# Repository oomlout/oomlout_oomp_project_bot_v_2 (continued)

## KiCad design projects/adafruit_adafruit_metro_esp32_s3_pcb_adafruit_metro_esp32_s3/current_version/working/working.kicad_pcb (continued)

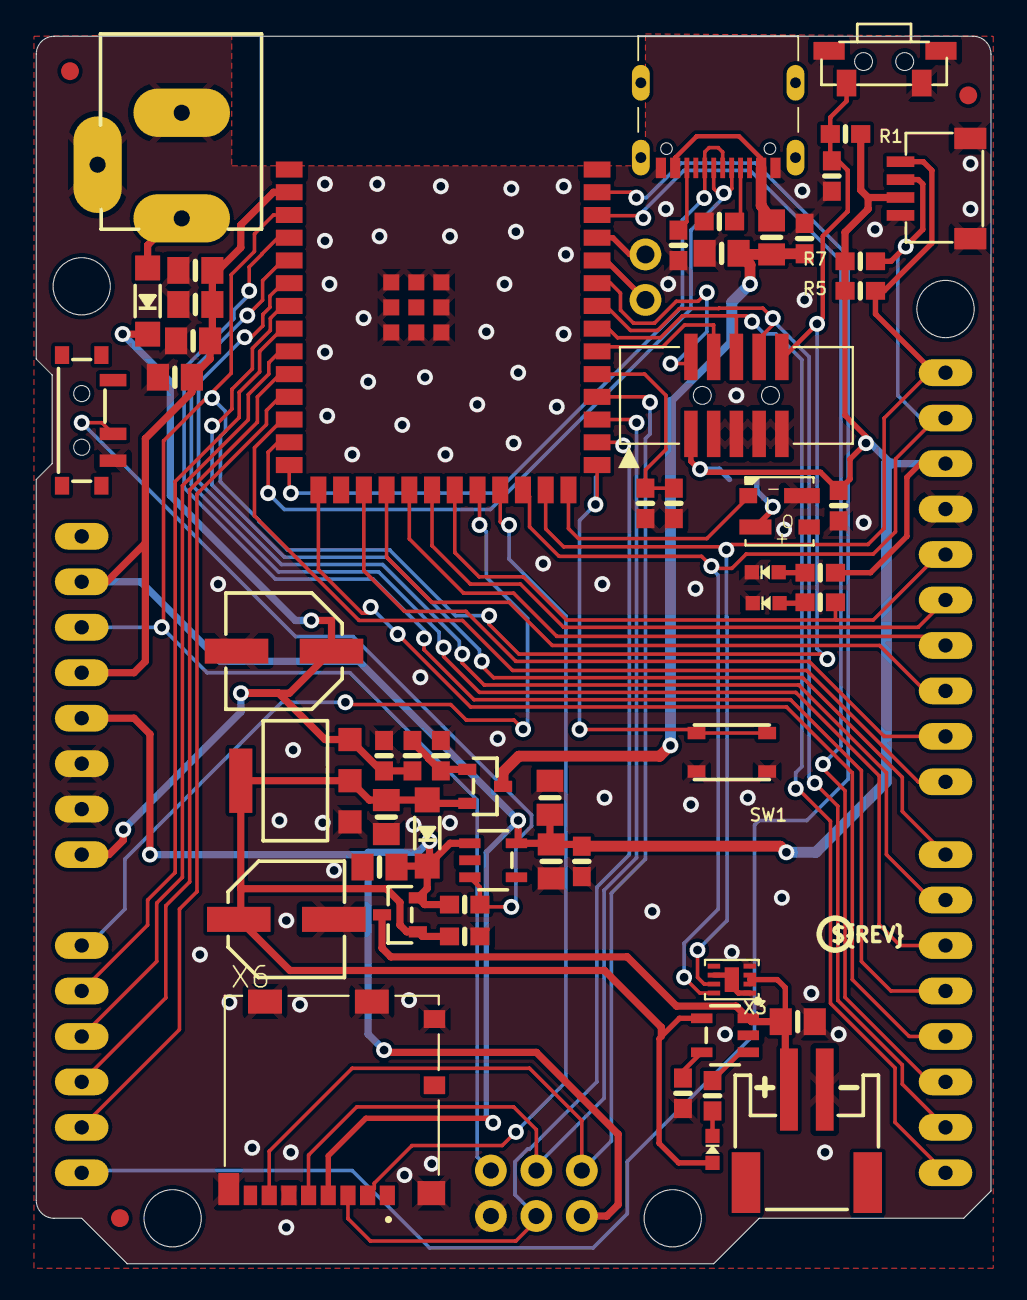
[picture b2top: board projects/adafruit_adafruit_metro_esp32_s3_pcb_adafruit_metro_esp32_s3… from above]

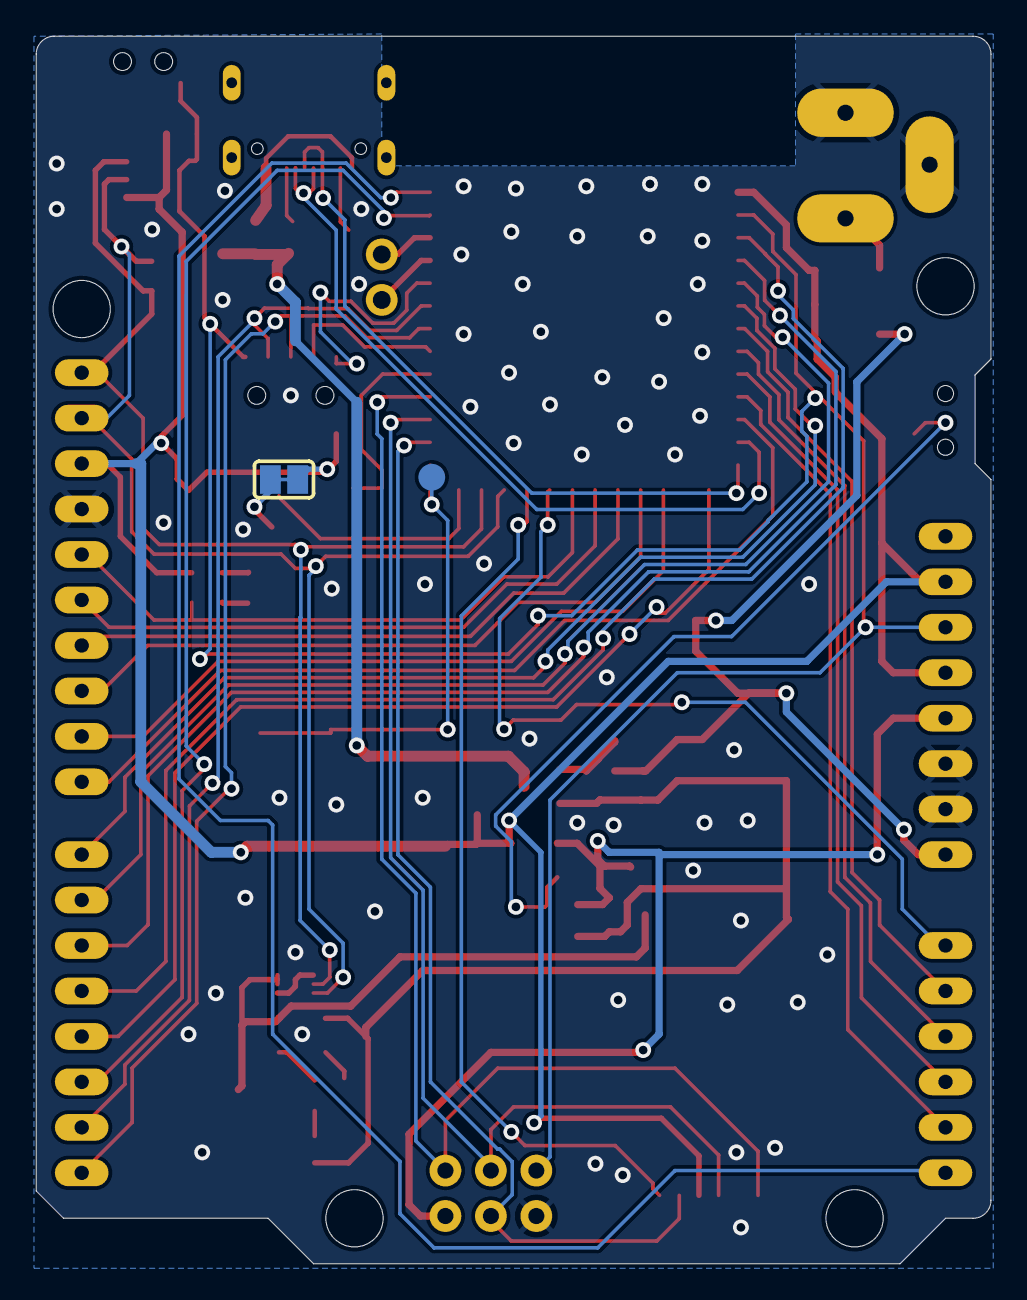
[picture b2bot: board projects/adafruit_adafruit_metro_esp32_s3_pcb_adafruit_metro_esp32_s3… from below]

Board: 2 copper layers, 53.3 x 68.6 mm, 73 parts (3 on the bottom side), 55 nets.

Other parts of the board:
@HOLE0, @HOLE1, @HOLE2, @HOLE3: (no value)
U$15: PCBFEAT-REV-040
U$52: METROS3_TOP
U$58: METROS3_BOT

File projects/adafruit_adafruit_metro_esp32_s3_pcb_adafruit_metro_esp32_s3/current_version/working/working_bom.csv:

"Id";"Designator";"Footprint";"Quantity";"Designation";"Supplier and ref";
1;"Q2,Q1";"SOT23-R";2;"DMG3415U-7";;;
2;"C15,C2,C12";"0603-NO";3;"0.1uF";;;
3;"R5,R6,R2,R7,R9,R1";"0603-NO";6;"10K";;;
4;"X3";"TDFN8_2X2MM";1;"MAX17048/T";;;
5;"C3,C17,C7,C13,C11,C4,C18,C10,C1,C8";"0805-NO";10;"10uF";;;
6;"X5";"DCJACK_2MM_PTH";1;"2.1mm";;;
7;"SW1";"BTN_RKB2_4.6X2.8";1;"RKB2";;;
8;"U4";"SOT23-5";1;"AP2112(3.3V)";;;
9;"@HOLE2,@HOLE0,@HOLE3,@HOLE1";"";4;"";;;
10;"JP2";"1X02_ROUND";1;"UART";;;
11;"L0";"CHIPLED_0603_NOOUTLINE";1;"RED";;;
12;"SW4";"SPDT_SMT_SSSS811101";1;"SPDT R/A";;;
13;"R17";"0603-NO";1;"1Meg";;;
14;"U2";"SOT23-5";1;"MCP73831T-2ACI/OT";;;
15;"U1";"SOT223-R";1;"NCP1117ST50T3G";;;
16;"R12,R15,R16,R14";"0603-NO";4;"100K";;;
17;"ON0";"CHIPLED_0603_NOOUTLINE";1;"GREEN";;;
18;"U5";"S3-WROOM32";1;"ESP32-S3-WROOM";;;
19;"R8,R3";"0603-NO";2;"5.1K";;;
20;"IOH0";"1X10_OVALWAVE";1;"1x10 F";;;
21;"R4";"0603-NO";1;"2.2K";;;
22;"FD1,FD2,FD3";"FIDUCIAL_1MM";3;"FIDUCIAL_1MM";;;
23;"X1";"JSTPH2_BATT";1;"JSTPH";;;
24;"CHG1";"CHIPLED_0603_NOOUTLINE";1;"ORANGE";;;
25;"PC2,PC1";"PANASONIC_D";2;"47uF/25V";;;
26;"X6";"MOLEX_104031-0811";1;"MicroSD";;;
27;"POWER0,IOL0";"1X08_OVALWAVE";2;"1x8 F";;;
28;"AD0";"1X06_OVALWAVE";1;"1x6 F";;;
29;"C14,C5,C6";"0603-NO";3;"1uF";;;
30;"SW3";"SPST_TACTILE_RA";1;"RA_TACT";;;
31;"CONN1";"JST_SH4";1;"STEMMA_I2C_QT";;;
32;"F2";"0805-NO";1;"500mA";;;
33;"X2";"2X05_1.27MM_BOX_POSTS";1;"2x5 0.05in";;;
34;"D1,D4";"SOD-123";2;"MBR540";;;
35;"U$15";"PCBFEAT-REV-040";1;"";;;
36;"ICSP0";"2X03_ROUND_70MIL";1;"3x2 M";;;
37;"U$52";"METROS3_TOP";1;"";;;
38;"X4";"USB_C_CUSB31-CFM2AX-01-X";1;"USB C";;;
39;"LED1";"LED3535_FULLPADS";1;"WS2812B_3535FULL";;;
40;"TP1";"TESTPOINT_ROUND_1.5MM_NO";1;"";;;
41;"U$58";"METROS3_BOT";1;"";;;
42;"SJ1";"SOLDERJUMPER_CLOSEDWIRE";1;"";;;

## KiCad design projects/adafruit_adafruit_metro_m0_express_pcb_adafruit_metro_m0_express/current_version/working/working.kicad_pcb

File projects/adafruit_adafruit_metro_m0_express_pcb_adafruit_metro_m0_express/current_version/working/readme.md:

# adafruit_metro_m0_express_pcb
 
## summary 
* id: adafruit_adafruit_metro_m0_express_pcb_adafruit_metro_m0_express
* user: adafruit
* name: adafruit_metro_m0_express_pcb
* board: adafruit_metro_m0_express
* repo: https://github.com/adafruit/Adafruit-Metro-M0-Express-PCB

* src_file_repo_sch: 
* src_file_repo_sch_link: https://github.com/adafruit/Adafruit-Metro-M0-Express-PCB/tree/master/
* full details link: https://github.com/oomlout/oomlout_oomp_project_bot_v_2/tree/main/projects/adafruit_adafruit_metro_m0_express_pcb_adafruit_metro_m0_express/current_version/working  

## schematic  
  
[schematic (pdf)](working_schematic.pdf) 

## pcb  

[board (pdf)](working.pdf)  

## working_bom
| Id | Designator | Footprint | Quantity | Designation | Supplier and ref |  | None | 
| --- | --- | --- | --- | --- | --- | --- | --- | 
| 1 | FB2,FB1 | 0805-NO | 2 | FERRITE |  |  | [''] | 
| 2 | R1 | RESPACK_4X0603 | 1 | 100K |  |  | [''] | 
| 3 | @HOLE0,@HOLE1,@HOLE3,@HOLE2 |  | 4 |  |  |  | [''] | 
| 4 | FD1,FD2,FD3 | FIDUCIAL_1MM | 3 | FIDUCIAL_1MM |  |  | [''] | 
| 5 | X3 | 4UCONN_20329_V2 | 1 | 20329 |  |  | [''] | 
| 6 | U$14 | PCBFEAT-REV-040 | 1 |  |  |  | [''] | 
| 7 | C11,C14,C6,C10,C4,C13,C12,C2,C9 | 0805-NO | 9 | 0.1uF |  |  | [''] | 
| 8 | R11,R3 | 0805-NO | 2 | 330R |  |  | [''] | 
| 9 | X5 | DCJACK_2MM_PTH | 1 | 2.1mm |  |  | [''] | 
| 10 | PC2 | PANASONIC_D | 1 | 47uF+/6.3V+ |  |  | [''] | 
| 11 | R4 | 0805-NO | 1 | 1K |  |  | [''] | 
| 12 | SW1 | SPDT_SMT_SSSS811101 | 1 |  |  |  | [''] | 
| 13 | TXLED0,RXLED0 | CHIPLED_0805_NOOUTLINE | 2 | YELLOW |  |  | [''] | 
| 14 | IOL0,POWER0 | 1X08_OVALWAVE | 2 | 20610 |  |  | [''] | 
| 15 | R7,R5 | 0805-NO | 2 | 10K |  |  | [''] | 
| 16 | L0 | CHIPLED_0805_NOOUTLINE | 1 | RED |  |  | [''] | 
| 17 | U1 | SOT223-R | 1 | NCP1117ST50T3G |  |  | [''] | 
| 18 | F2 | R1206 | 1 | 500mA |  |  | [''] | 
| 19 | IOH0 | 1X10_OVALWAVE | 1 | 20611 |  |  | [''] | 
| 20 | X2 | 2X05_1.27MM_BOX_POSTS | 1 | 2x5 0.05 SWD" |  |  | [''] | 
| 21 | T2,TR1 | SOT-23 | 2 | DMP3098L-7 |  |  | [''] | 
| 22 | C1 | 0805-NO | 1 | 1uF |  |  | [''] | 
| 23 | C7,C5 | 0805-NO | 2 | 22pF |  |  | [''] | 
| 24 | U$30 | METRO_M0_FRONT | 1 |  |  |  | [''] | 
| 25 | JP1 | 1X01_ROUND | 1 |  |  |  | [''] | 
| 26 | C8,C3 | 0805-NO | 2 | 10uF |  |  | [''] | 
| 27 | ICSP0 | 2X03_ROUND_70MIL | 1 | 3x2 M |  |  | [''] | 
| 28 | R2 | RESPACK_4X0603 | 1 | 1K |  |  | [''] | 
| 29 | PC1 | PANASONIC_D | 1 | 47uF/25V |  |  | [''] | 
| 30 | Y1 | CRYSTAL_8X3.8 | 1 | 32.768KHz |  |  | [''] | 
| 31 | U$1 | TQFN48_7MM | 1 | ATSAMD21G18_QFN |  |  | [''] | 
| 32 | AD0 | 1X06_OVALWAVE | 1 | 20609 |  |  | [''] | 
| 33 | LED1 | LED3535 | 1 | WS2812B3535 |  |  | [''] | 
| 34 | ON0 | CHIPLED_0805_NOOUTLINE | 1 | GREEN |  |  | [''] | 
| 35 | RESET0 | EVQ-Q2 | 1 | EVQQ 6mm |  |  | [''] | 
| 36 | D1 | SOD-123 | 1 | MBR120 |  |  | [''] | 
| 37 | IC3 | SOT23-5 | 1 | 74LVC1G125D |  |  | [''] | 
| 38 | U3 | SOIC8_208MIL | 1 | SPI Flash |  |  | [''] | 
| 39 | U2 | SOT23-DBV | 1 | AP2112K-3.3 |  |  | [''] | 
| 40 | U$11 | METRO_M0_BACK | 1 |  |  |  | [''] | 
| 41 | TP1,TP2 | TESTPOINT_ROUND_1.5MM | 2 |  |  |  | [''] | 
| 42 | GROUND1 | SJ | 1 |  |  |  | [''] | 

## bom_schematic
| Ref | Qnty | Value | Cmp name | Footprint | Description | Vendor | DNP | 
| --- | --- | --- | --- | --- | --- | --- | --- | 
| AD0 | 1 | 20609 | HEADER-1X6OVALWAVE | working:1X06_OVALWAVE |  |  |  | 
| C1 | 1 | 1uF | CAP_CERAMIC0805-NOOUTLINE | working:0805-NO |  |  |  | 
| C2, C4, C6, C9, C10, C11, C12, C13, C14 | 9 | 0.1uF | CAP_CERAMIC0805-NOOUTLINE | working:0805-NO |  |  |  | 
| C3, C8 | 2 | 10uF | CAP_CERAMIC0805-NOOUTLINE | working:0805-NO |  |  |  | 
| C5, C7 | 2 | 22pF | CAP_CERAMIC0805-NOOUTLINE | working:0805-NO |  |  |  | 
| D1 | 1 | MBR120 | DIODE-SCHOTTKYSOD-123 | working:SOD-123 |  |  |  | 
| F2 | 1 | 500mA | PTCFUSE-1206 | working:R1206 |  |  |  | 
| FB1, FB2 | 2 | FERRITE | FERRITE-0805NO | working:0805-NO |  |  |  | 
| FD1, FD2, FD3 | 3 | FIDUCIAL_1MM | FIDUCIAL_1MM | working:FIDUCIAL_1MM |  |  |  | 
| GROUND1 | 1 | SJ | SJ | working:SJ |  |  |  | 
| IC3 | 1 | 741G125DBV | 741G125DBV | working:SOT23-5 |  |  |  | 
| ICSP0 | 1 | 3x2 M | HEADER-2X3 | working:2X03_ROUND_70MIL |  |  |  | 
| IOH0 | 1 | 20611 | HEADER-1X10OVALWAVE | working:1X10_OVALWAVE |  |  |  | 
| IOL0 | 1 | 20610 | HEADER-1X8OVALWAVE | working:1X08_OVALWAVE |  |  |  | 
| JP1 | 1 | HEADER-1X1ROUND | HEADER-1X1ROUND | working:1X01_ROUND |  |  |  | 
| L0 | 1 | RED | LED0805_NOOUTLINE | working:CHIPLED_0805_NOOUTLINE |  |  |  | 
| LED1 | 1 | WS2812B3535 | WS2812B3535 | working:LED3535 |  |  |  | 
| ON0 | 1 | GREEN | LED0805_NOOUTLINE | working:CHIPLED_0805_NOOUTLINE |  |  |  | 
| PC1 | 1 | 47uF/25V | CAP_ELECTROLYTICPANASONIC_D | working:PANASONIC_D |  |  |  | 
| PC2 | 1 | 47uF+/6.3V+ | CAP_ELECTROLYTICPANASONIC_D | working:PANASONIC_D |  |  |  | 
| POWER0 | 1 | 20610 | HEADER-1X8OVALWAVE | working:1X08_OVALWAVE |  |  |  | 
| R1 | 1 | 100K | RESISTOR_4PACK | working:RESPACK_4X0603 |  |  |  | 
| R2 | 1 | 1K | RESISTOR_4PACK | working:RESPACK_4X0603 |  |  |  | 
| R3, R11 | 2 | 330R | RESISTOR0805_NOOUTLINE | working:0805-NO |  |  |  | 
| R4 | 1 | 1K | RESISTOR0805_NOOUTLINE | working:0805-NO |  |  |  | 
| R5, R7 | 2 | 10K | RESISTOR0805_NOOUTLINE | working:0805-NO |  |  |  | 
| RESET0 | 1 | EVQQ 6mm | SWITCH_TACT_SMT | working:EVQ-Q2 |  |  |  | 
| RXLED0 | 1 | YELLOW | LED0805_NOOUTLINE | working:CHIPLED_0805_NOOUTLINE |  |  |  | 
| SW1 | 1 | SWITCH_SPDT | SWITCH_SPDT | working:SPDT_SMT_SSSS811101 |  |  |  | 
| T2 | 1 | DMP3098L-7 | PMOSSOT23 | working:SOT-23 |  |  |  | 
| TP1, TP2 | 2 | TESTPOINTROUND1.5MM | TESTPOINTROUND1.5MM | working:TESTPOINT_ROUND_1.5MM |  |  |  | 
| TR1 | 1 | DMP3098L-7 | 0297_PMV48XP | working:SOT-23 |  |  |  | 
| TXLED0 | 1 | YELLOW | LED0805_NOOUTLINE | working:CHIPLED_0805_NOOUTLINE |  |  |  | 
| U1 | 1 | NCP1117ST50T3G | LM1117SOT223-REFLOW | working:SOT223-R |  |  |  | 
| U2 | 1 | LP2985-XXDBVR | LP2985-XXDBVR | working:SOT23-DBV |  |  |  | 
| U3 | 1 | SPI Flash | SPIFLASH_SOIC8208MIL | working:SOIC8_208MIL |  |  |  | 
| U$1 | 1 | ATSAMD21J_QFN | ATSAMD21J_QFN | working:TQFN48_7MM |  |  |  | 
| X2 | 1 | 2x5 0.05" SWD | JTAG-CORTEXBOXPOSTS | working:2X05_1.27MM_BOX_POSTS |  |  |  | 
| X3 | 1 | USB_W_SHIELD_V2 | USB_W_SHIELD_V2 | working:4UCONN_20329_V2 |  |  |  | 
| X5 | 1 | 2.1mm | DCBARRELPTH | working:DCJACK_2MM_PTH |  |  |  | 
| Y1 | 1 | 32.768KHz | CRYSTAL8.0X3.8 | working:CRYSTAL_8X3.8 |  |  |  |

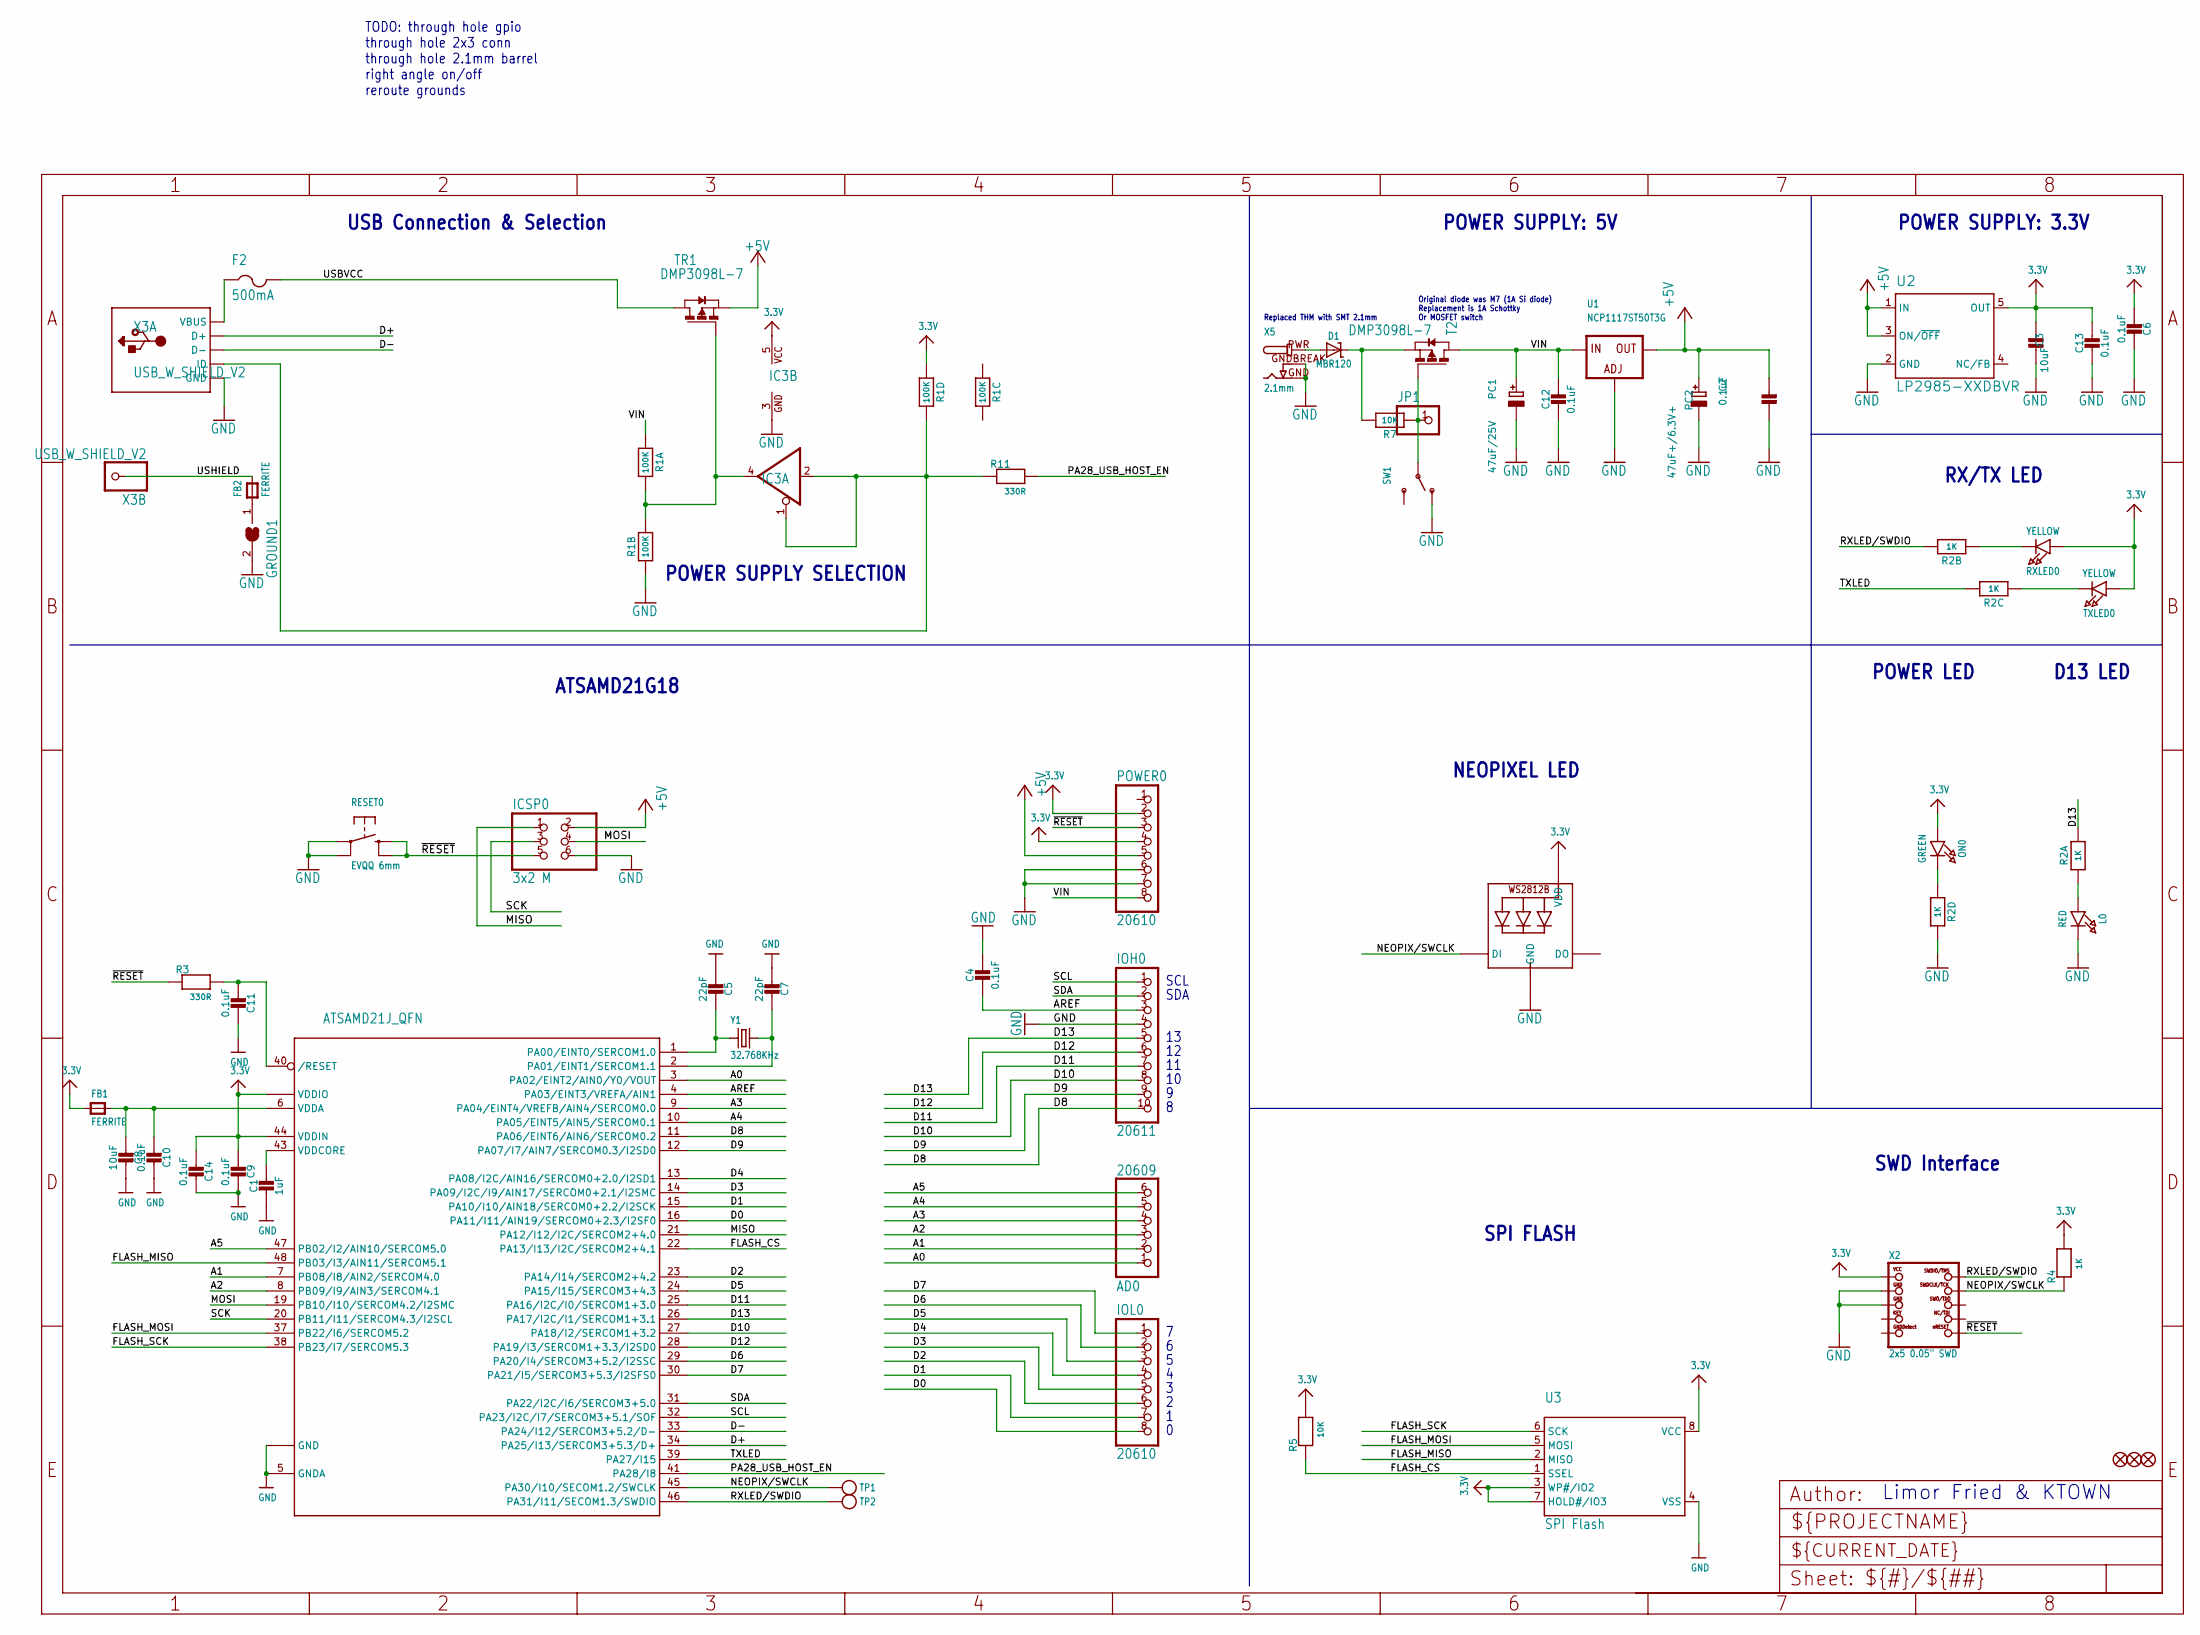
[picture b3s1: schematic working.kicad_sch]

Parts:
AD0: 20609; 1X06_OVALWAVE
C1: 1uF; 0805-NO
C2, C4, C6, C9, C10, C11, C12, C13, C14: 0.1uF; 0805-NO
C3, C8: 10uF; 0805-NO
C5, C7: 22pF; 0805-NO
D1: MBR120; SOD-123
F2: 500mA; R1206
FB1, FB2: FERRITE; 0805-NO
FD1, FD2, FD3: FIDUCIAL_1MM
GROUND1: SJ
IC3: 741G125DBV; SOT23-5
ICSP0: 3x2 M; 2X03_ROUND_70MIL
IOH0: 20611; 1X10_OVALWAVE
IOL0: 20610; 1X08_OVALWAVE
JP1: HEADER-1X1ROUND; 1X01_ROUND
L0: RED; CHIPLED_0805_NOOUTLINE
LED1: WS2812B3535; LED3535
ON0: GREEN; CHIPLED_0805_NOOUTLINE
PC1: 47uF/25V; PANASONIC_D
PC2: 47uF+/6.3V+; PANASONIC_D
POWER0: 20610; 1X08_OVALWAVE
R1: 100K; RESPACK_4X0603
R2: 1K; RESPACK_4X0603
R3, R11: 330R; 0805-NO
R4: 1K; 0805-NO
R5, R7: 10K; 0805-NO
RESET0: EVQQ 6mm; EVQ-Q2
RXLED0: YELLOW; CHIPLED_0805_NOOUTLINE
SW1: SWITCH_SPDT; SPDT_SMT_SSSS811101
T2: DMP3098L-7; SOT-23
TP1, TP2: TESTPOINTROUND1.5MM; TESTPOINT_ROUND_1.5MM
TR1: DMP3098L-7; SOT-23
TXLED0: YELLOW; CHIPLED_0805_NOOUTLINE
U1: NCP1117ST50T3G; SOT223-R
U2: LP2985-XXDBVR; SOT23-DBV
U3: SPI Flash; SOIC8_208MIL
U$1: ATSAMD21J_QFN; TQFN48_7MM
X2: 2x5 0.05" SWD; 2X05_1.27MM_BOX_POSTS
X3: USB_W_SHIELD_V2; 4UCONN_20329_V2
X5: 2.1mm; DCJACK_2MM_PTH
Y1: 32.768KHz; CRYSTAL_8X3.8

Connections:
3.3V: C3.2, C6.2, C9.2, C13.1, C14.2, FB1.1, IC3.5 (VCC), LED1.2 (VDD), ON0.A, POWER0.2, POWER0.4, R1.4 (1), R4.2, R5.2, RXLED0.A, TXLED0.A, U2.5 (OUT), U3.3 (WP#/IO2), U3.7 (HOLD#/IO3), U3.8 (VCC), U$1.17 (VDDIO), U$1.36 (VDDIO), U$1.44 (VDDIN), X2.1 (VCC)
+5V: C2.2, ICSP0.2, PC2.+, POWER0.5, TR1.2 (S), U1.2 (OUT), U1.4 (OUT), U2.1 (IN), U2.3 (ON/~OFF)
A0: AD0.1, U$1.3 (PA02/EINT2/AIN0/Y0/VOUT)
A1: AD0.2, U$1.7 (PB08/I8/AIN2/SERCOM4.0)
A2: AD0.3, U$1.8 (PB09/I9/AIN3/SERCOM4.1)
A3: AD0.4, U$1.9 (PA04/EINT4/VREFB/AIN4/SERCOM0.0)
A4: AD0.5, U$1.10 (PA05/EINT5/AIN5/SERCOM0.1)
A5: AD0.6, U$1.47 (PB02/I2/AIN10/SERCOM5.0)
AREF: C4.2, IOH0.3, U$1.4 (PA03/EINT3/VREFA/AIN1)
AVCC: C8.2, C10.2, FB1.2, U$1.6 (VDDA)
D0: IOL0.8, U$1.16 (PA11/I11/AIN19/SERCOM0+2.3/I2SF0)
D1: IOL0.7, U$1.15 (PA10/I10/AIN18/SERCOM0+2.2/I2SCK)
D2: IOL0.6, U$1.23 (PA14/I14/SERCOM2+4.2)
D3: IOL0.5, U$1.14 (PA09/I2C/I9/AIN17/SERCOM0+2.1/I2SMC)
D4: IOL0.4, U$1.13 (PA08/I2C/AIN16/SERCOM0+2.0/I2SD1)
D5: IOL0.3, U$1.24 (PA15/I15/SERCOM3+4.3)
D6: IOL0.2, U$1.29 (PA20/I4/SERCOM3+5.2/I2SSC)
D7: IOL0.1, U$1.30 (PA21/I5/SERCOM3+5.3/I2SFS0)
D8: IOH0.10, U$1.11 (PA06/EINT6/AIN6/SERCOM0.2)
D9: IOH0.9, U$1.12 (PA07/I7/AIN7/SERCOM0.3/I2SD0)
D10: IOH0.8, U$1.27 (PA18/I2/SERCOM1+3.2)
D11: IOH0.7, U$1.25 (PA16/I2C/I0/SERCOM1+3.0)
D12: IOH0.6, U$1.28 (PA19/I3/SERCOM1+3.3/I2SD0)
D13: IOH0.5, R2.8 (2), U$1.26 (PA17/I2C/I1/SERCOM1+3.1)
D+: U$1.34 (PA25/I13/SERCOM3+5.3/D+), X3.D+
D-: U$1.33 (PA24/I12/SERCOM3+5.2/D-), X3.D-
FLASH_CS: R5.1, U3.1 (SSEL), U$1.22 (PA13/I13/I2C/SERCOM2+4.1)
FLASH_MISO: U3.2 (MISO), U$1.48 (PB03/I3/AIN11/SERCOM5.1)
FLASH_MOSI: U3.5 (MOSI), U$1.37 (PB22/I6/SERCOM5.2)
FLASH_SCK: U3.6 (SCK), U$1.38 (PB23/I7/SERCOM5.3)
GND: C1.2, C2.1, C3.1, C4.1, C5.2, C6.1, C7.2, C8.1, C9.1, C10.1, C11.1, C12.2, C13.2, C14.1, GROUND1.2, IC3.3 (GND), ICSP0.6, IOH0.4, L0.C, LED1.4 (GND), PC1.-, PC2.-, POWER0.6, POWER0.7, R1.2 (1), R2.5 (2), RESET0.A, RESET0.A' (P1), SW1.A (O), U1.1 (ADJ), U2.2 (GND), U3.4 (VSS), U$1.5 (GNDA), U$1.18 (GND), U$1.35 (GND), U$1.42 (GND), U$1.THERMAL (GND), X2.3 (GND@1), X2.5 (GND@2), X3.GND, X5.GND, X5.GNDBREAK
MISO: ICSP0.1, U$1.21 (PA12/I12/I2C/SERCOM2+4.0)
MOSI: ICSP0.4, U$1.19 (PB10/I10/SERCOM4.2/I2SMC)
unnamed: L0.A, R2.1
unnamed: FB2.1, GROUND1.1
unnamed: ON0.C, R2.4 (1)
unnamed: C5.1, U$1.1 (PA00/EINT0/SERCOM1.0), Y1.P$1 (1)
unnamed: R2.2 (1), RXLED0.C
unnamed: C7.1, U$1.2 (PA01/EINT1/SERCOM1.1), Y1.P$4 (2)
unnamed: R2.3 (1), TXLED0.C
unnamed: C11.2, R3.2, U$1.40 (/RESET)
unnamed: D1.A, X5.PWR
unnamed: IC3.1 (OE), IC3.2 (I), R1.5 (2), R11.1, X3.ID
unnamed: IC3.4 (O), R1.7 (2), R1.8 (2), TR1.3 (G)
unnamed: JP1.1, R7.1, SW1.B, T2.3 (G)
unnamed: D1.C, R7.2, T2.2 (S)
NEOPIX/SWCLK: LED1.1 (DI), R4.1, TP1.P$1, U$1.45 (PA30/I10/SECOM1.2/SWCLK), X2.4 (SWDCLK)
PA28_USB_HOST_EN: R11.2, U$1.41 (PA28/I8)
RXLED/SWDIO: R2.7 (2), TP2.P$1, U$1.46 (PA31/I11/SECOM1.3/SWDIO), X2.2 (SWDIO)
SCK: ICSP0.3, U$1.20 (PB11/I11/SERCOM4.3/I2SCL)
SCL: IOH0.1, U$1.32 (PA23/I2C/I7/SERCOM3+5.1/SOF)
SDA: IOH0.2, U$1.31 (PA22/I2C/I6/SERCOM3+5.0)
TXLED: R2.6 (2), U$1.39 (PA27/I15)
USBVCC: F2.2, TR1.1 (D)
USHIELD: FB2.2, X3.BASE@1 (1), X3.BASE@2 (1), X3.SPRT@1 (1), X3.SPRT@2 (1), X3.SPRT@3 (1), X3.SPRT@4 (1)
VBUS: F2.1, X3.VBUS
VDDCORE: C1.1, U$1.43 (VDDCORE)
VIN: C12.1, PC1.+, POWER0.8, R1.1, T2.1 (D), U1.3 (IN)
~RESET: ICSP0.5, POWER0.3, R3.1, RESET0.B (S), RESET0.B' (S1), X2.10 (NRESET)

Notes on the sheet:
SWD Interface
Original diode was M7 (1A Si diode) Replacement is 1A Schottky Or MOSFET switch
TODO: through hole gpio through hole 2x3 conn through hole 2.1mm barrel right angle on/off reroute grounds
USB Connection & Selection
SDA
Replaced THM with SMT 2.1mm
SCL
D13 LED
POWER LED
POWER SUPPLY SELECTION
ATSAMD21G18
Limor Fried & KTOWN
NEOPIXEL LED
RX/TX LED
POWER SUPPLY: 3.3V
POWER SUPPLY: 5V
SPI FLASH

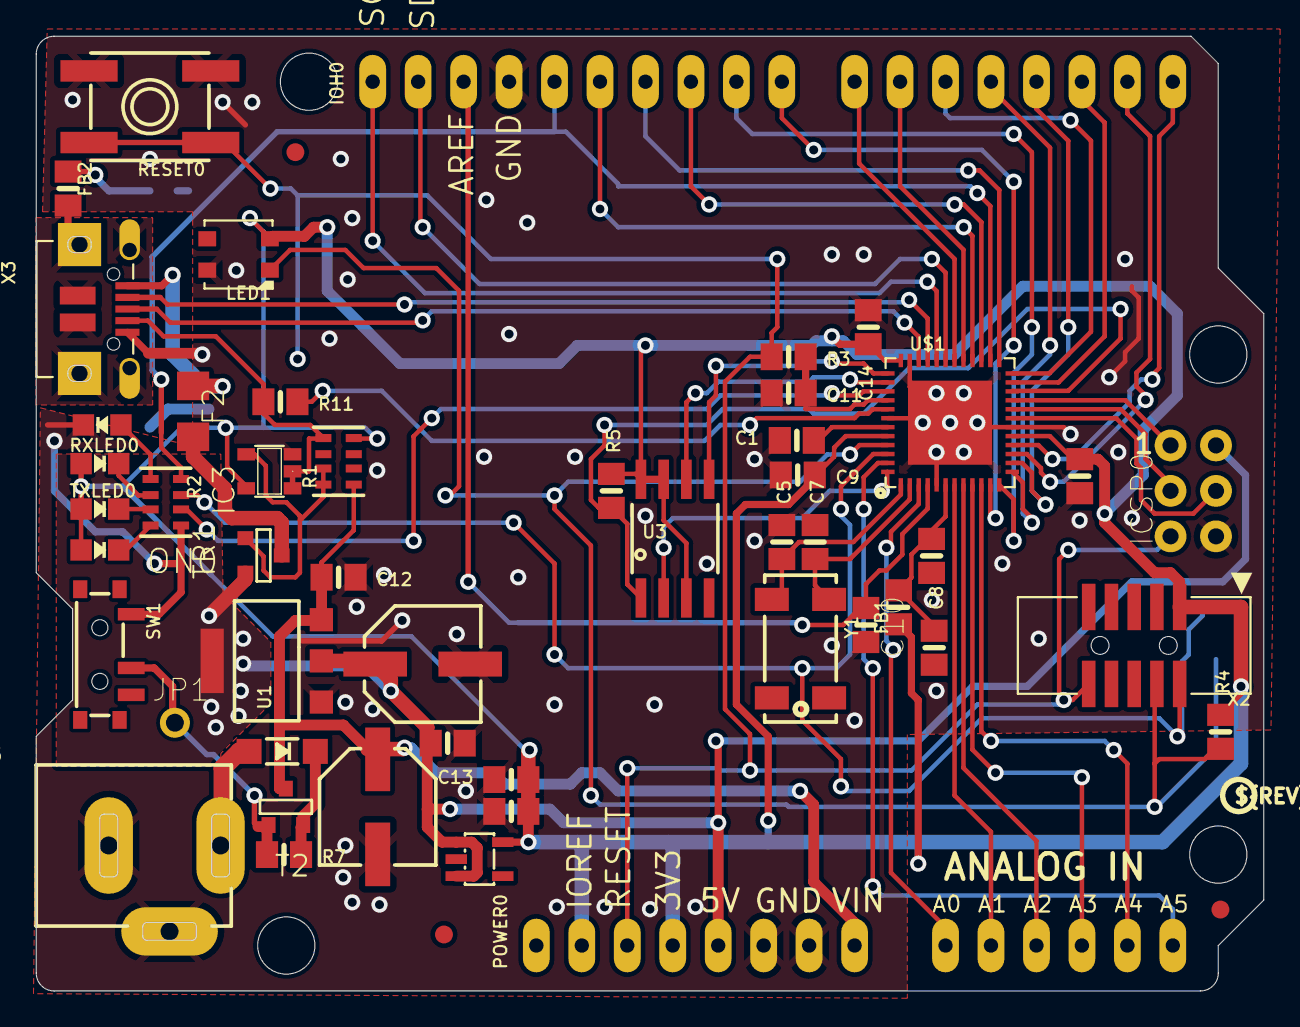
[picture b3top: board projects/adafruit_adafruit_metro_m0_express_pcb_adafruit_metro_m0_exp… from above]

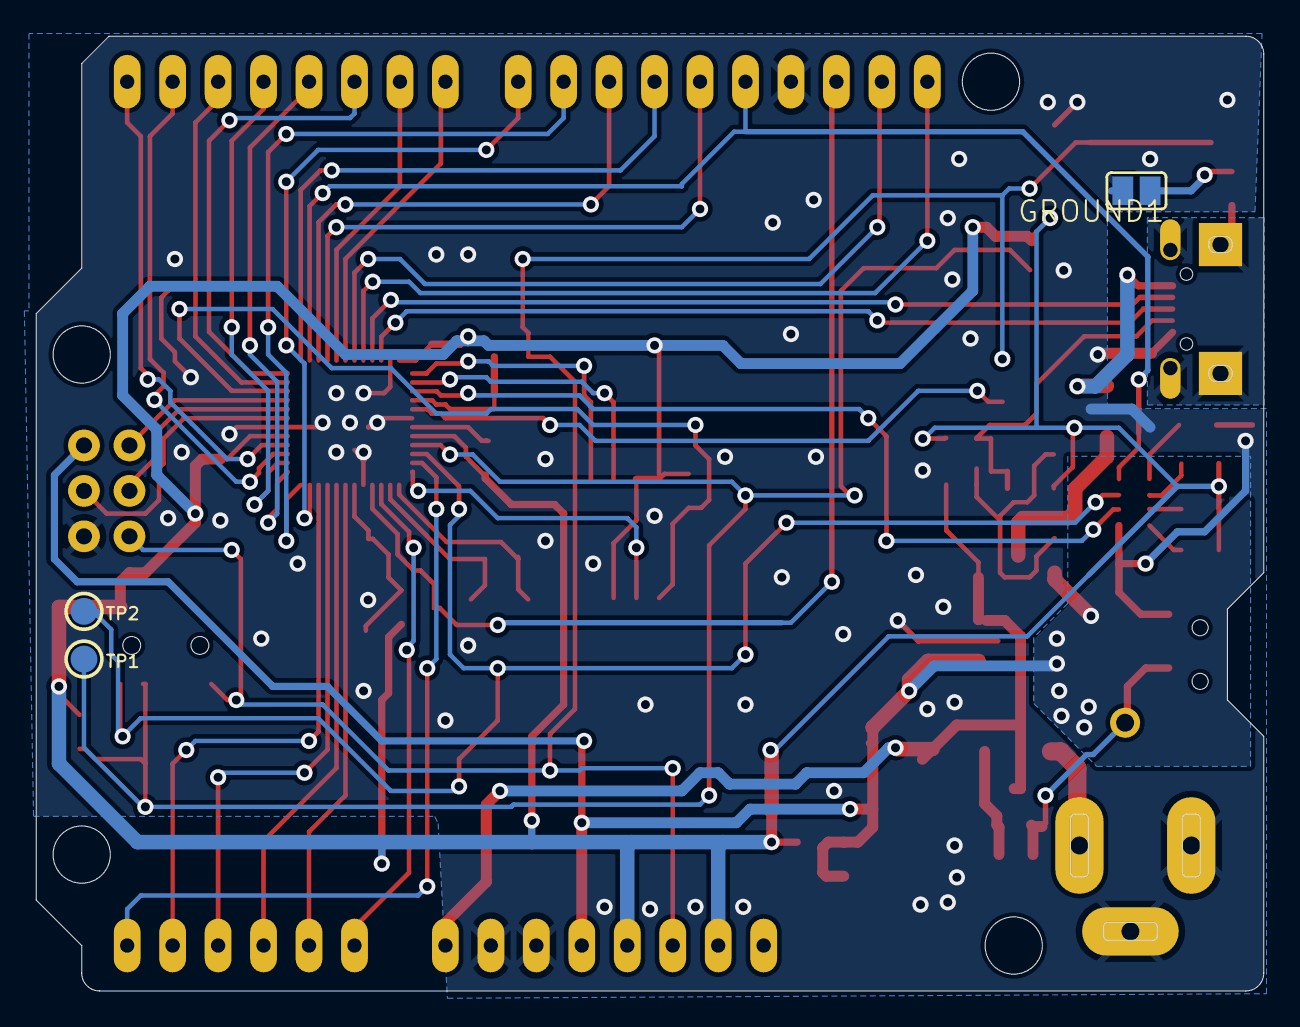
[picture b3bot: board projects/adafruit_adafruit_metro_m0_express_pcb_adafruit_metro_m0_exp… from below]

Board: 2 copper layers, 68.6 x 53.3 mm, 64 parts (4 on the bottom side), 59 nets.

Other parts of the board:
@HOLE0, @HOLE1, @HOLE2, @HOLE3: (no value)
U$11: METRO_M0_BACK
U$14: PCBFEAT-REV-040
U$30: METRO_M0_FRONT

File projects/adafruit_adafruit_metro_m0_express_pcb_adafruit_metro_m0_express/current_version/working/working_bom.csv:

"Id";"Designator";"Footprint";"Quantity";"Designation";"Supplier and ref";
1;"FB2,FB1";"0805-NO";2;"FERRITE";;;
2;"R1";"RESPACK_4X0603";1;"100K";;;
3;"@HOLE0,@HOLE1,@HOLE3,@HOLE2";"";4;"";;;
4;"FD1,FD2,FD3";"FIDUCIAL_1MM";3;"FIDUCIAL_1MM";;;
5;"X3";"4UCONN_20329_V2";1;"20329";;;
6;"U$14";"PCBFEAT-REV-040";1;"";;;
7;"C11,C14,C6,C10,C4,C13,C12,C2,C9";"0805-NO";9;"0.1uF";;;
8;"R11,R3";"0805-NO";2;"330R";;;
9;"X5";"DCJACK_2MM_PTH";1;"2.1mm";;;
10;"PC2";"PANASONIC_D";1;"47uF+/6.3V+";;;
11;"R4";"0805-NO";1;"1K";;;
12;"SW1";"SPDT_SMT_SSSS811101";1;"";;;
13;"TXLED0,RXLED0";"CHIPLED_0805_NOOUTLINE";2;"YELLOW";;;
14;"IOL0,POWER0";"1X08_OVALWAVE";2;"20610";;;
15;"R7,R5";"0805-NO";2;"10K";;;
16;"L0";"CHIPLED_0805_NOOUTLINE";1;"RED";;;
17;"U1";"SOT223-R";1;"NCP1117ST50T3G";;;
18;"F2";"R1206";1;"500mA";;;
19;"IOH0";"1X10_OVALWAVE";1;"20611";;;
20;"X2";"2X05_1.27MM_BOX_POSTS";1;"2x5 0.05" SWD";;;
21;"T2,TR1";"SOT-23";2;"DMP3098L-7";;;
22;"C1";"0805-NO";1;"1uF";;;
23;"C7,C5";"0805-NO";2;"22pF";;;
24;"U$30";"METRO_M0_FRONT";1;"";;;
25;"JP1";"1X01_ROUND";1;"";;;
26;"C8,C3";"0805-NO";2;"10uF";;;
27;"ICSP0";"2X03_ROUND_70MIL";1;"3x2 M";;;
28;"R2";"RESPACK_4X0603";1;"1K";;;
29;"PC1";"PANASONIC_D";1;"47uF/25V";;;
30;"Y1";"CRYSTAL_8X3.8";1;"32.768KHz";;;
31;"U$1";"TQFN48_7MM";1;"ATSAMD21G18_QFN";;;
32;"AD0";"1X06_OVALWAVE";1;"20609";;;
33;"LED1";"LED3535";1;"WS2812B3535";;;
34;"ON0";"CHIPLED_0805_NOOUTLINE";1;"GREEN";;;
35;"RESET0";"EVQ-Q2";1;"EVQQ 6mm";;;
36;"D1";"SOD-123";1;"MBR120";;;
37;"IC3";"SOT23-5";1;"74LVC1G125D";;;
38;"U3";"SOIC8_208MIL";1;"SPI Flash";;;
39;"U2";"SOT23-DBV";1;"AP2112K-3.3";;;
40;"U$11";"METRO_M0_BACK";1;"";;;
41;"TP1,TP2";"TESTPOINT_ROUND_1.5MM";2;"";;;
42;"GROUND1";"SJ";1;"";;;
